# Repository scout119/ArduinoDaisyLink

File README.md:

ArduinoDaisyLink
================
This is implementation of the Gadgeteer DaisyLink protocol on Atmega328. 
This will allow to build Gadgeteer DaisyLink modules using AVR chips and program them from Arduino IDE.

There is a reference design of Smart Piezo Gadgeteer Module that uses the Arduino DL libary.

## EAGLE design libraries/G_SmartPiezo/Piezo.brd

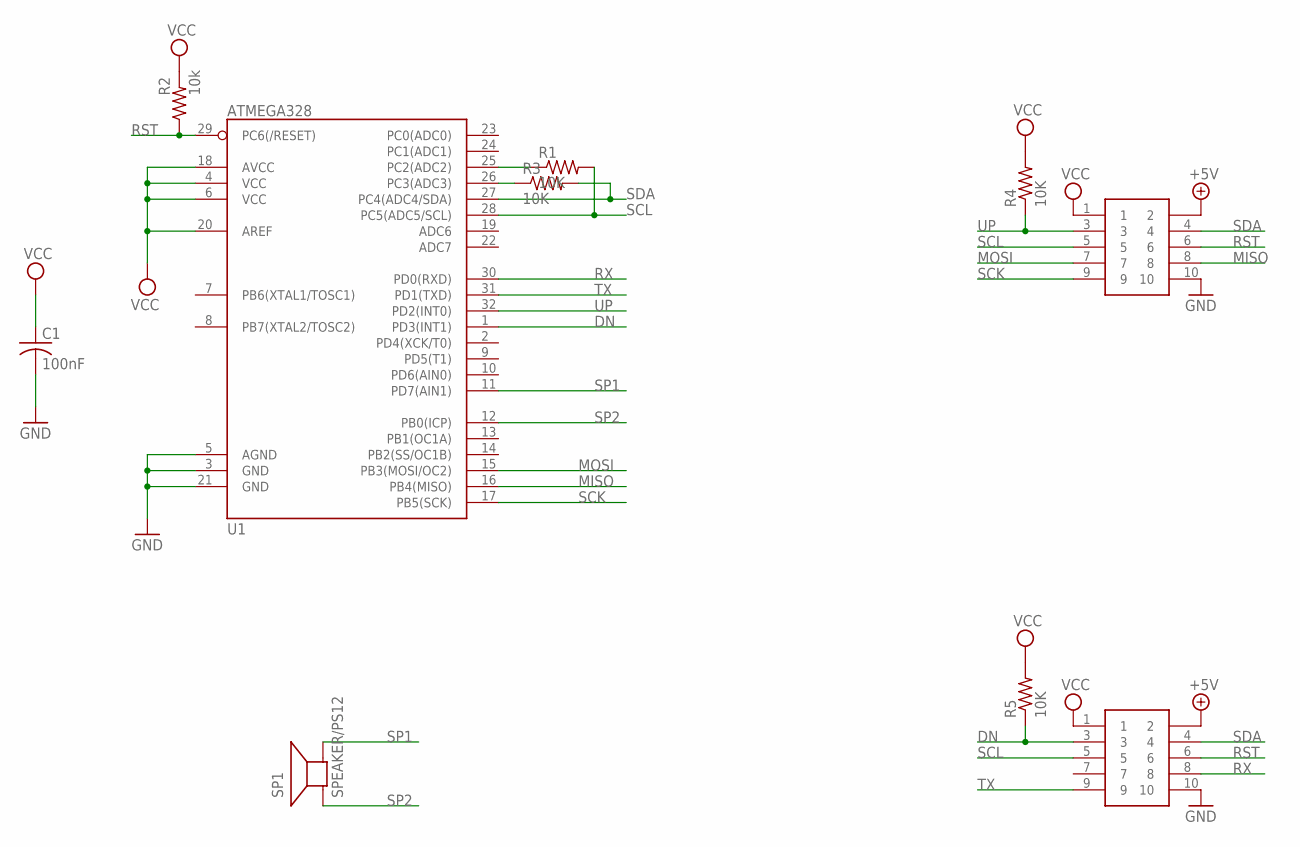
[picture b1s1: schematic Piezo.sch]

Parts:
*: SHF105SM; SHF105DSM
C1: 100nF; C0603K
R1, R3, R4, R5: 10K; R0603
R2: 10k; R0603
SP1: SPEAKER/PS12; PS12
U1: ATMEGA328; TQFP32-08
XY: SHF105SM; SHF105DSM

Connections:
+5V: *.2, XY.2
DN: *.3, R5.1, U1.1 (PD3(INT1))
GND: *.10, C1.2, U1.3 (GND), U1.5 (AGND), U1.21 (GND), XY.10
MISO: U1.16 (PB4(MISO)), XY.8
MOSI: U1.15 (PB3(MOSI/OC2)), XY.7
unnamed: R1.1, U1.25 (PC2(ADC2))
unnamed: R3.1, U1.26 (PC3(ADC3))
RST: *.6, R2.1, U1.29 (PC6(/RESET)), XY.6
RX: *.8, U1.30 (PD0(RXD))
SCK: U1.17 (PB5(SCK)), XY.9
SCL: *.5, R1.2, U1.28 (PC5(ADC5/SCL)), XY.5
SDA: *.4, R3.2, U1.27 (PC4(ADC4/SDA)), XY.4
SP1: SP1.P$2 (-), U1.11 (PD7(AIN1))
SP2: SP1.P$1 (+), U1.12 (PB0(ICP))
TX: *.9, U1.31 (PD1(TXD))
UP: R4.1, U1.32 (PD2(INT0)), XY.3
VCC: *.1, C1.1, R2.2, R4.2, R5.2, U1.4 (VCC), U1.6 (VCC), U1.18 (AVCC), U1.20 (AREF), XY.1

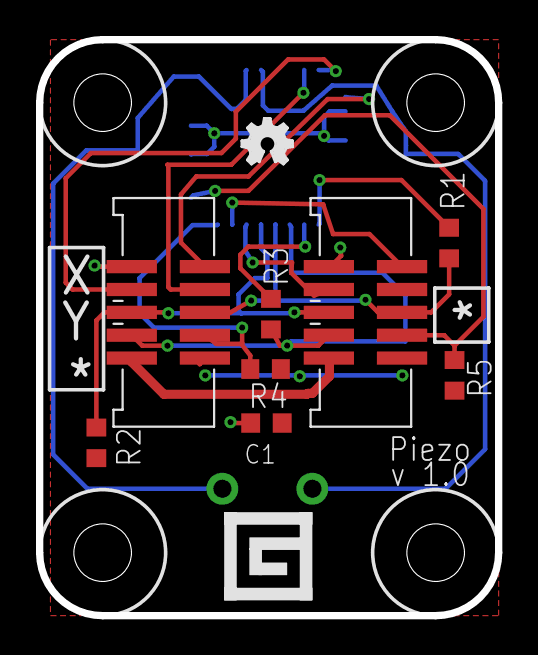
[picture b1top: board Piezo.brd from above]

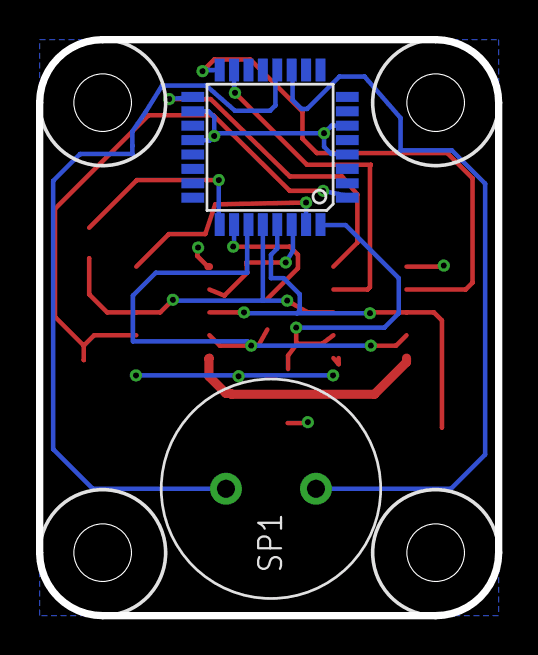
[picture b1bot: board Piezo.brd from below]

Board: 2 copper layers, 25.5 x 32.0 mm, 18 parts (2 on the bottom side), 17 nets.

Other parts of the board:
U$1, U$2, U$3, U$4: HOLE3.2
U$5: LABEL_XYASTERISK
U$6: LABEL_ASTERISK
U$7: GADGETEER_LOGO_SMALL
U$8: OSHW_LOGO

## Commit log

2014-01-12 DaisyLink implementation on Arduino
2014-01-18 The latest version of the module's eagle files

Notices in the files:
parts and their libraries:
SparkFun: Licensing: CC v3.0 Share-Alike You are welcome to use this library for commercial purposes.
